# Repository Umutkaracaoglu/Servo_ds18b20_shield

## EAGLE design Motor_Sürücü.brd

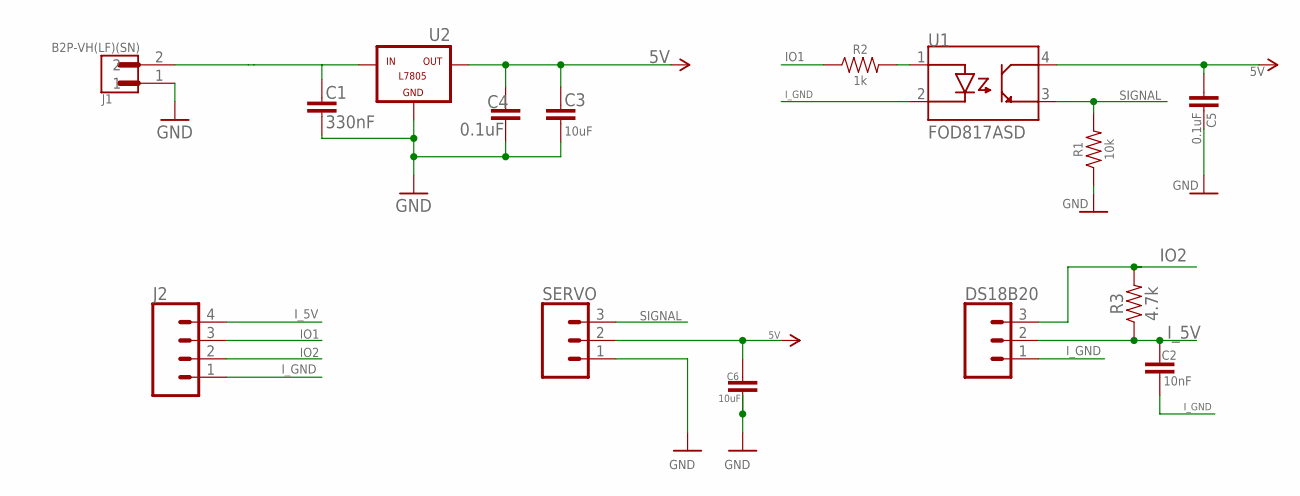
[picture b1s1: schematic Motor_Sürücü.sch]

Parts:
C1: 330nF; 0603
C2: 10nF; 0603
C3, C6: 10uF; 0603
C4, C5: 0.1uF; 0603
DS18B20: CONN_03; 1X03
J1: B2P-VH(LF)(SN); JST_B2P-VH(LF)(SN)
J2: CONN_04; 1X04
R1: 10k; 0603
R2: 1k; 0603
R3: 4.7k; 0603
SERVO: CONN_03; 1X03
U1: FOD817ASD; SOIC254P1016X385-4N
U2: L7805; 78XXL

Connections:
5V: C3.1, C4.1, C5.2, C6.1, SERVO.2, U1.4 (COLLECTOR), U2.OUT
GND: C1.2, C3.2, C4.2, C5.1, C6.2, J1.1, R1.1, SERVO.1, U2.GND
IO1: J2.3, R2.1
IO2: DS18B20.3, J2.2, R3.2
I_5V: C2.1, DS18B20.2, J2.4, R3.1
I_GND: C2.2, DS18B20.1, J2.1, U1.2 (CATHODE)
unnamed: R2.2, U1.1 (ANODE)
unnamed: C1.1, J1.2, U2.IN
SIGNAL: R1.2, SERVO.3, U1.3 (EMITTER)

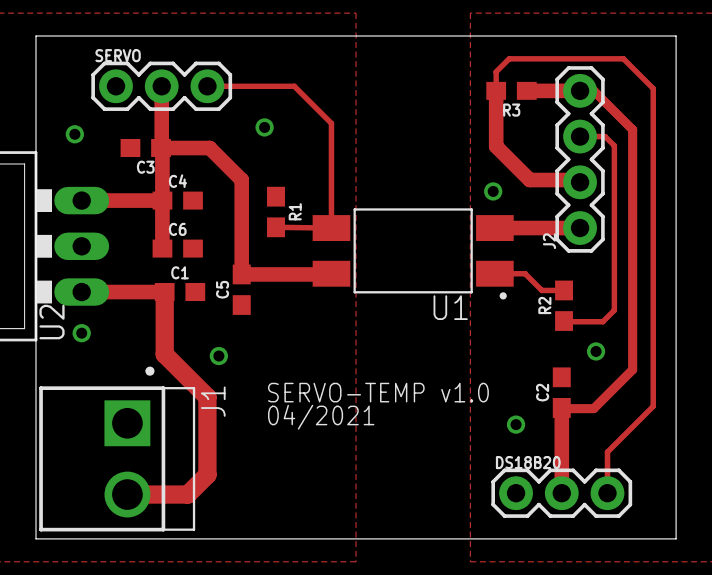
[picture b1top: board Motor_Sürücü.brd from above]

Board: 2 copper layers, 35.6 x 27.9 mm, 15 parts (0 on the bottom side), 9 nets.

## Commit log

2021-09-26 Motor_Sürücü

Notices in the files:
parts and their libraries:
SparkFun-Capacitors: Licensing: CC v3.0 Share-Alike You are welcome to use this library for commercial purposes.
SparkFun-Connectors: Licensing: Creative Commons ShareAlike 4.0 International - https://creativecommons.org/licenses/by-sa/4.0
